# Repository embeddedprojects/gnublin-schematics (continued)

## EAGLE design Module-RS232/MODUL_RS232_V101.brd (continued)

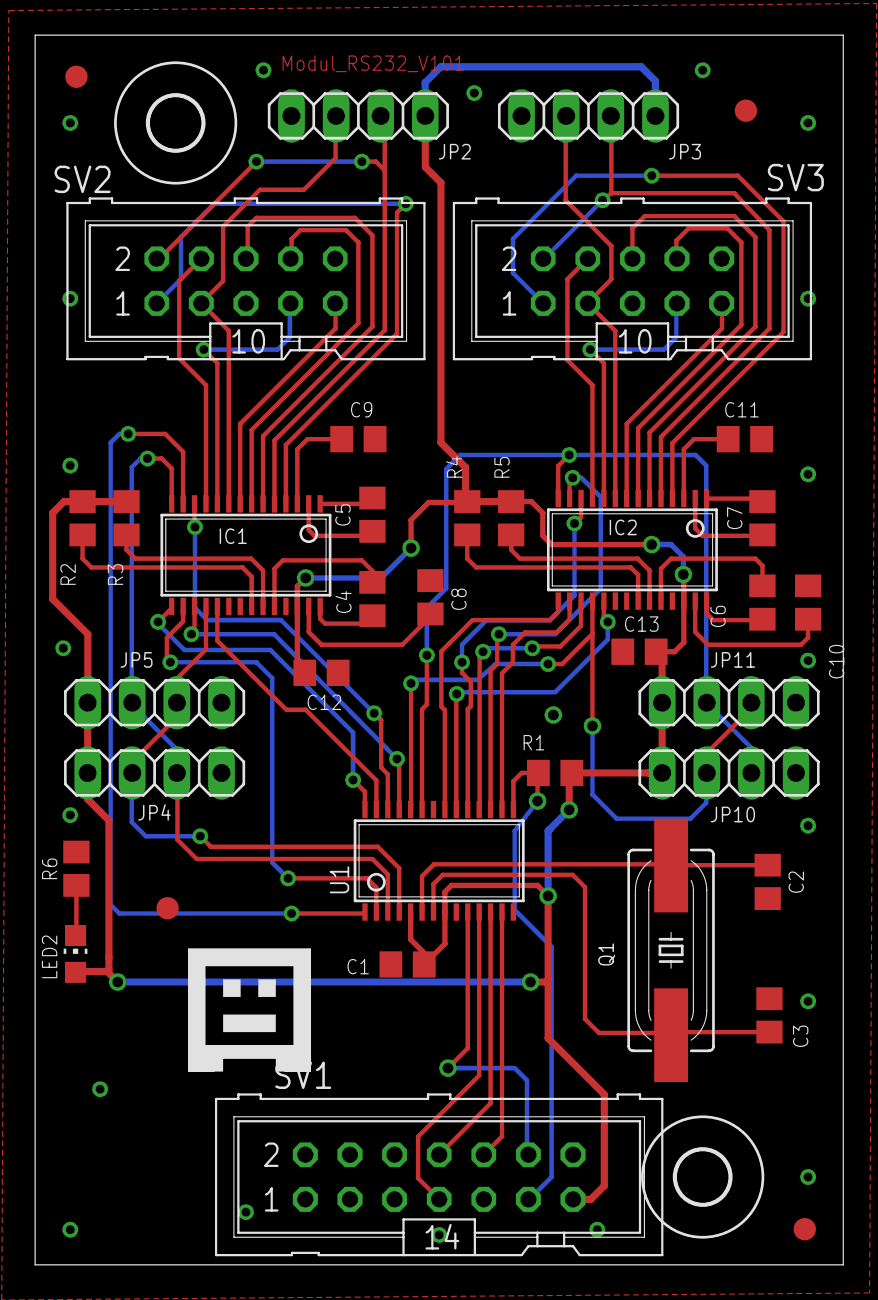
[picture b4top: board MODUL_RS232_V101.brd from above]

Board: 2 copper layers, 46.0 x 70.0 mm, 40 parts (0 on the bottom side), 58 nets.

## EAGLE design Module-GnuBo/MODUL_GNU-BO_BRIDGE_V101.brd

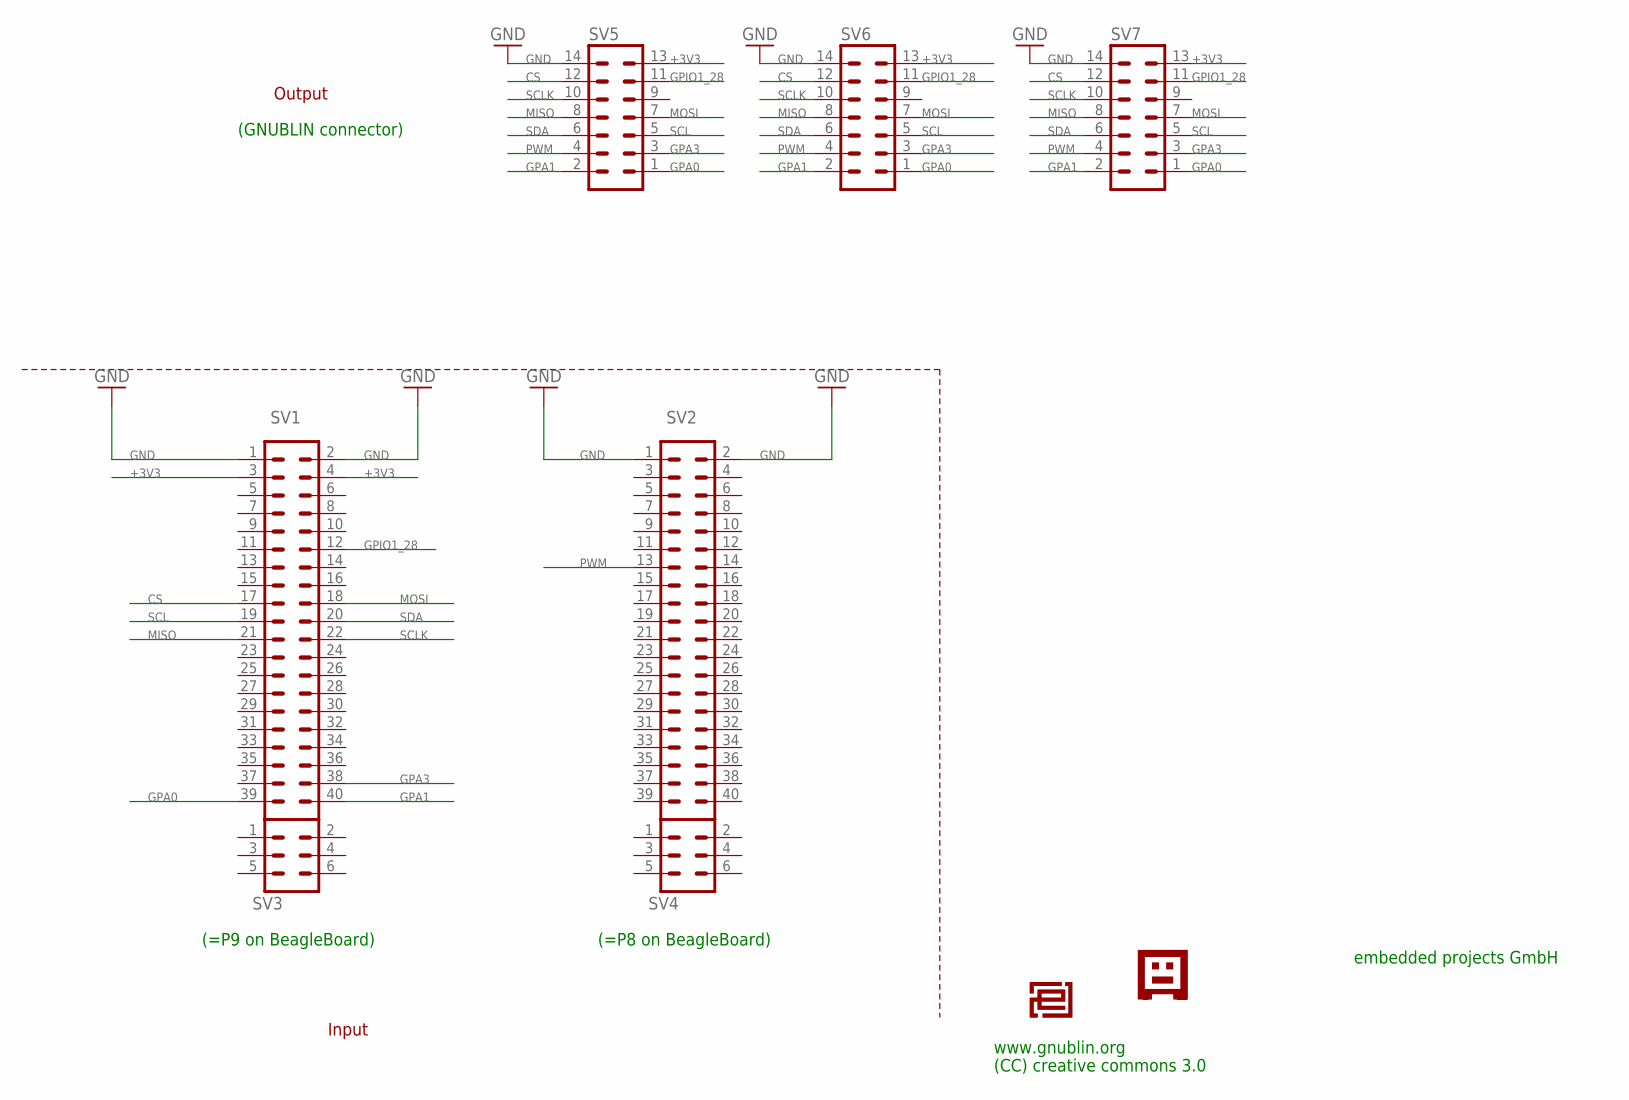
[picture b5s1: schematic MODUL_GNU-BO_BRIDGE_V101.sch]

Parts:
SV1, SV2: MA20-2
SV3, SV4: MA03-2
SV5, SV6, SV7: ML14
U$2: EPLOGOSIEB; EPLOGOSIEBDRUCK
U$3: GNUBLINLOGOSIEB; GNUSIEBDRUCK

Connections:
+3V3: SV1.3, SV1.4, SV5.13, SV6.13, SV7.13
CS: SV1.17, SV5.12, SV6.12, SV7.12
GND: SV1.1, SV1.2, SV2.1, SV2.2, SV5.14, SV6.14, SV7.14
GPA0: SV1.39, SV5.1, SV6.1, SV7.1
GPA1: SV1.40, SV5.2, SV6.2, SV7.2
GPA3: SV1.38, SV5.3, SV6.3, SV7.3
GPIO1_28: SV1.12, SV5.11, SV6.11, SV7.11
MISO: SV1.21, SV5.8, SV6.8, SV7.8
MOSI: SV1.18, SV5.7, SV6.7, SV7.7
PWM: SV2.13, SV5.4, SV6.4, SV7.4
SCL: SV1.19, SV5.5, SV6.5, SV7.5
SCLK: SV1.22, SV5.10, SV6.10, SV7.10
SDA: SV1.20, SV5.6, SV6.6, SV7.6

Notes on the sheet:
embedded projects GmbH
Input
Output
(=P9 on BeagleBoard)
(=P8 on BeagleBoard)
(GNUBLIN connector)
(CC) creative commons 3.0
www.gnublin.org

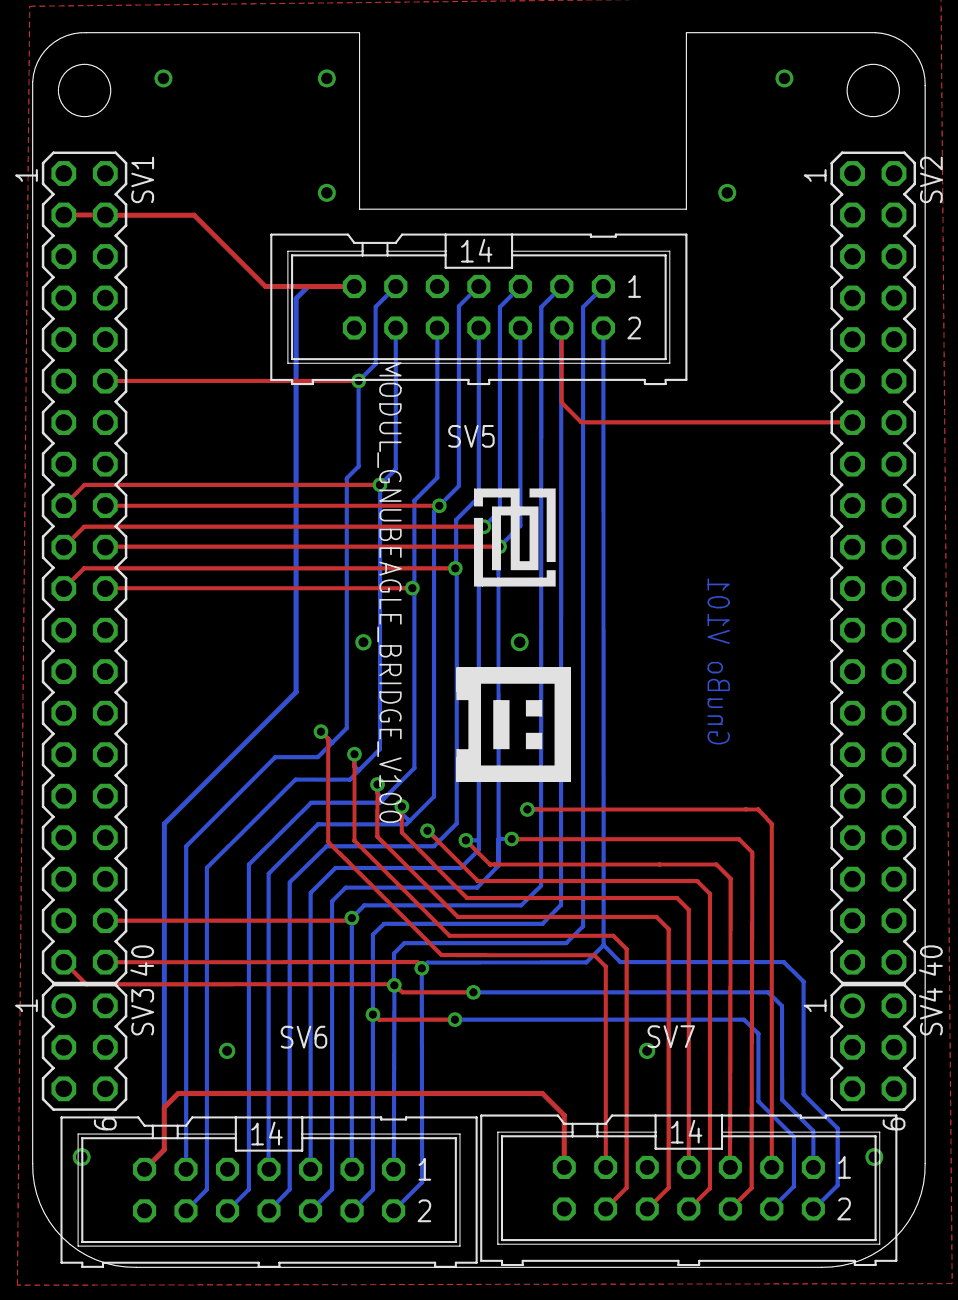
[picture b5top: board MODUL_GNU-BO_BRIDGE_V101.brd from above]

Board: 2 copper layers, 54.6 x 75.5 mm, 9 parts (0 on the bottom side), 13 nets.

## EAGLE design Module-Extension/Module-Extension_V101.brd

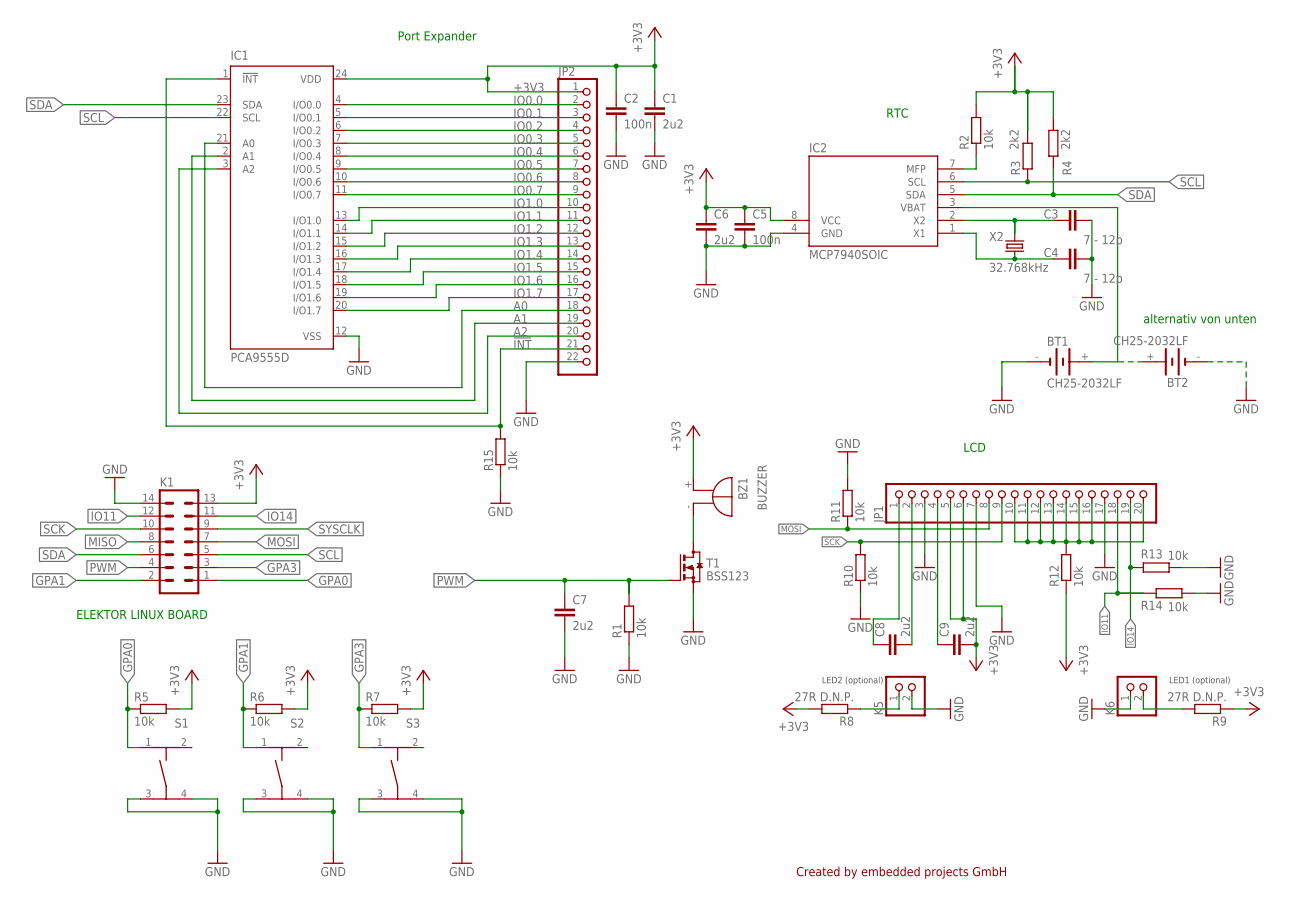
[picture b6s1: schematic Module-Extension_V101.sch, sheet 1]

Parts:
BT1, BT2: CH25-2032LF; CH25; FARNELL 2064715
BZ1: BUZZER; F/TMB
C1, C6, C7, C8, C9: 2u2; C0805
C2, C5: 100n; C0805
C3, C4: 7 - 12p; C0805
IC1: PCA9555D; SO24
IC2: MCP7940SOIC; SOIC-8
JP1: PINHD-1X20; 1X20
JP2: PINHD-1X22; 1X22
K1: ML14
K5, K6: PINHD-1X2; 1X02
R1, R2, R5, R6, R7, R10, R11, R12, R13, R14, R15: 10k; R0805
R3, R4: 2k2; R0805
R8, R9: 27R D.N.P.; R0805
S1, S2, S3: ERGAENZUNG_TASTER-9314_SMD
T1: BSS123; SOT23
X2: 32.768kHz; TC26H

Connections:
!INT: IC1.1 (!INT), JP2.21, R15.2
+3V3: BZ1.+, C1.1, C2.1, C5.1, C6.1, C9.2, IC1.24 (VDD), IC2.8 (VCC), JP1.5, JP1.6, JP2.1, K1.13, R2.2, R3.2, R4.2, R5.2, R6.2, R7.2, R8.2, R9.1, R12.1; also elsewhere on the board
A0: IC1.21 (A0), JP2.18
A1: IC1.2 (A1), JP2.19
A2: IC1.3 (A2), JP2.20
GND: BT1.-, BT2.-, C1.2, C2.2, C3.2, C4.2, C5.2, C6.2, C7.2, IC1.12 (VSS), IC2.4 (GND), JP1.3, JP1.7, JP1.17, JP2.22, K1.14, K5.2, K6.1, R1.1, R10.1, R11.2, R13.1, R14.1, R15.1, S1.3, S1.4, S2.3, S2.4, S3.3, S3.4, T1.2 (S); also elsewhere on the board
GPA0: K1.1, R5.1, S1.1
GPA1: K1.2, R6.1, S2.1
GPA3: K1.3, R7.1, S3.1
IO0.0: IC1.4 (I/O0.0), JP2.2
IO0.1: IC1.5 (I/O0.1), JP2.3
IO0.2: IC1.6 (I/O0.2), JP2.4
IO0.3: IC1.7 (I/O0.3), JP2.5
IO0.4: IC1.8 (I/O0.4), JP2.6
IO0.5: IC1.9 (I/O0.5), JP2.7
IO0.6: IC1.10 (I/O0.6), JP2.8
IO0.7: IC1.11 (I/O0.7), JP2.9
IO1.0: IC1.13 (I/O1.0), JP2.10
IO1.1: IC1.14 (I/O1.1), JP2.11
IO1.2: IC1.15 (I/O1.2), JP2.12
IO1.3: IC1.16 (I/O1.3), JP2.13
IO1.4: IC1.17 (I/O1.4), JP2.14
IO1.5: IC1.18 (I/O1.5), JP2.15
IO1.6: IC1.19 (I/O1.6), JP2.16
IO1.7: IC1.20 (I/O1.7), JP2.17
IO11: JP1.18, K1.12, R14.2
IO14: JP1.19, K1.11, R13.2
MISO: K1.8
MOSI: JP1.8, K1.7, R11.1
unnamed: C8.1, JP1.1
unnamed: BZ1.-, T1.3 (D)
unnamed: IC2.7 (MFP), R2.1
unnamed: C3.1, IC2.2 (X2), X2.1
unnamed: C8.2, JP1.2
unnamed: C9.1, JP1.4
unnamed: K5.1, R8.1
unnamed: K6.2, R9.2
unnamed: JP1.10, JP1.11, JP1.12, JP1.13, JP1.14, JP1.15, JP1.16, JP1.20, R12.2
unnamed: C4.1, IC2.1 (X1), X2.2
PWM: C7.1, K1.4, R1.2, T1.1 (G)
SCK: JP1.9, K1.10, R10.2
SCL: IC1.22 (SCL), IC2.6 (SCL), K1.5, R3.1
SDA: IC1.23 (SDA), IC2.5 (SDA), K1.6, R4.1
SYSCLK: K1.9
VBAT: BT1.+, BT2.+, IC2.3 (VBAT)

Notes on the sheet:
LCD
Port Expander
RTC
ELEKTOR LINUX BOARD
LED1 (optional)
LED2 (optional)
Created by embedded projects GmbH
alternativ von unten

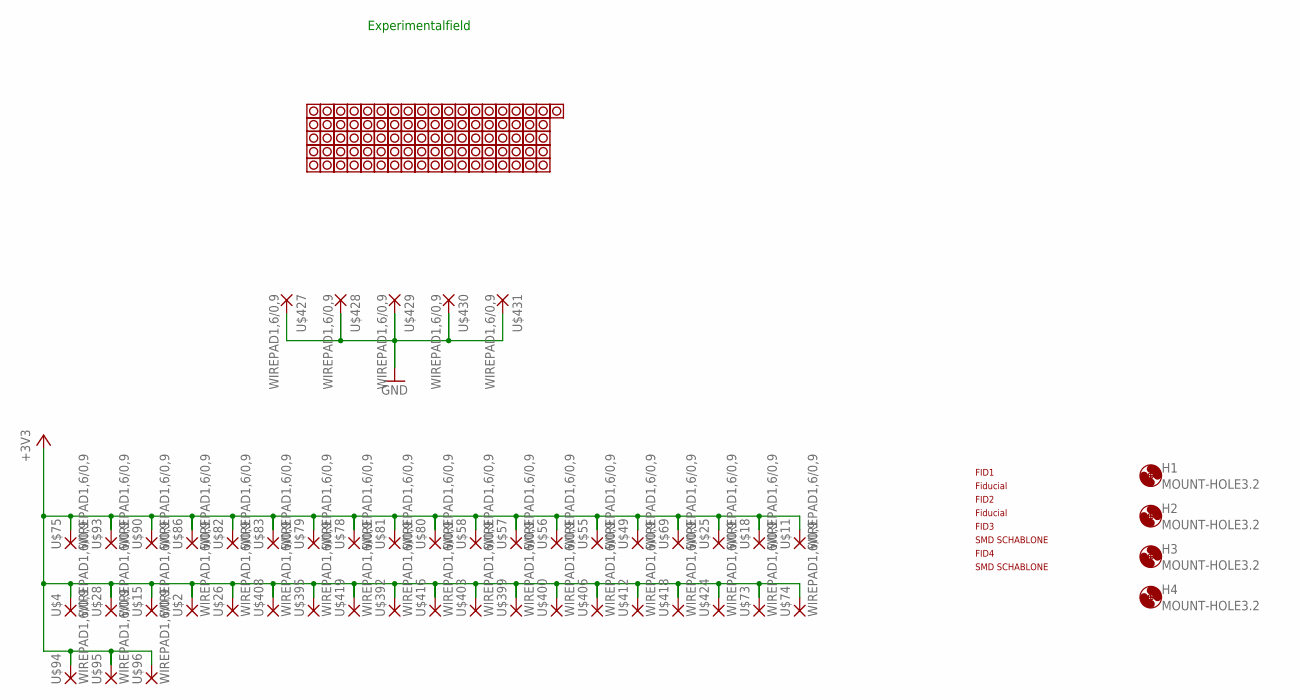
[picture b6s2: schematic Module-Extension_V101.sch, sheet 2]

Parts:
FID1, FID2, FID3, FID4: PASSERMARKEN_FIDUCIAL
H1, H2, H3, H4: MOUNT-HOLE3.2; 3,2
U$2, U$4, U$11, U$15, U$18, U$25, U$26, U$28, U$49, U$55, U$56, U$57, U$58, U$69, U$73, U$74, U$75, U$78, U$79, U$80, U$81, U$82, U$83, U$86, U$90, U$93, U$94, U$95, U$96, U$392, U$395, U$399, U$400, U$403, U$406, U$408, U$412, U$416, U$418, U$419, U$424, U$427, U$428, U$429, U$430, U$431: WIREPAD1,6/0,9; 1,6/0,9
U$3, U$5, U$6, U$7, U$8, U$9, U$10, U$12, U$13, U$14, U$16, U$17, U$19, U$20, U$21, U$22, U$23, U$24, U$27, U$29, U$30, U$31, U$32, U$33, U$34, U$35, U$36, U$37, U$38, U$39, U$40, U$41, U$42, U$43, U$44, U$45, U$46, U$47, U$48, U$50, U$51, U$52, U$53, U$54, U$59, U$60, U$61, U$62, U$63, U$64, U$65, U$66, U$67, U$68, U$70, U$71, U$72, U$76, U$77, U$84, U$85, U$87, U$88, U$89, U$91, U$92, U$391, U$393, U$394, U$396, U$397, U$398, U$401, U$402, U$404, U$405, U$407, U$409, U$410, U$411, U$413, U$414, U$415, U$417, U$420, U$421, U$422, U$423, U$425, U$426, U$432: VIAS

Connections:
+3V3: U$2.1, U$4.1, U$11.1, U$15.1, U$18.1, U$25.1, U$26.1, U$28.1, U$49.1, U$55.1, U$56.1, U$57.1, U$58.1, U$69.1, U$73.1, U$74.1, U$75.1, U$78.1, U$79.1, U$80.1, U$81.1, U$82.1, U$83.1, U$86.1, U$90.1, U$93.1, U$94.1, U$95.1, U$96.1, U$392.1, U$395.1, U$399.1, U$400.1, U$403.1, U$406.1, U$408.1, U$412.1, U$416.1, U$418.1, U$419.1, U$424.1; also elsewhere on the board
GND: U$427.1, U$428.1, U$429.1, U$430.1, U$431.1; also elsewhere on the board

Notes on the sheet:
Experimentalfield

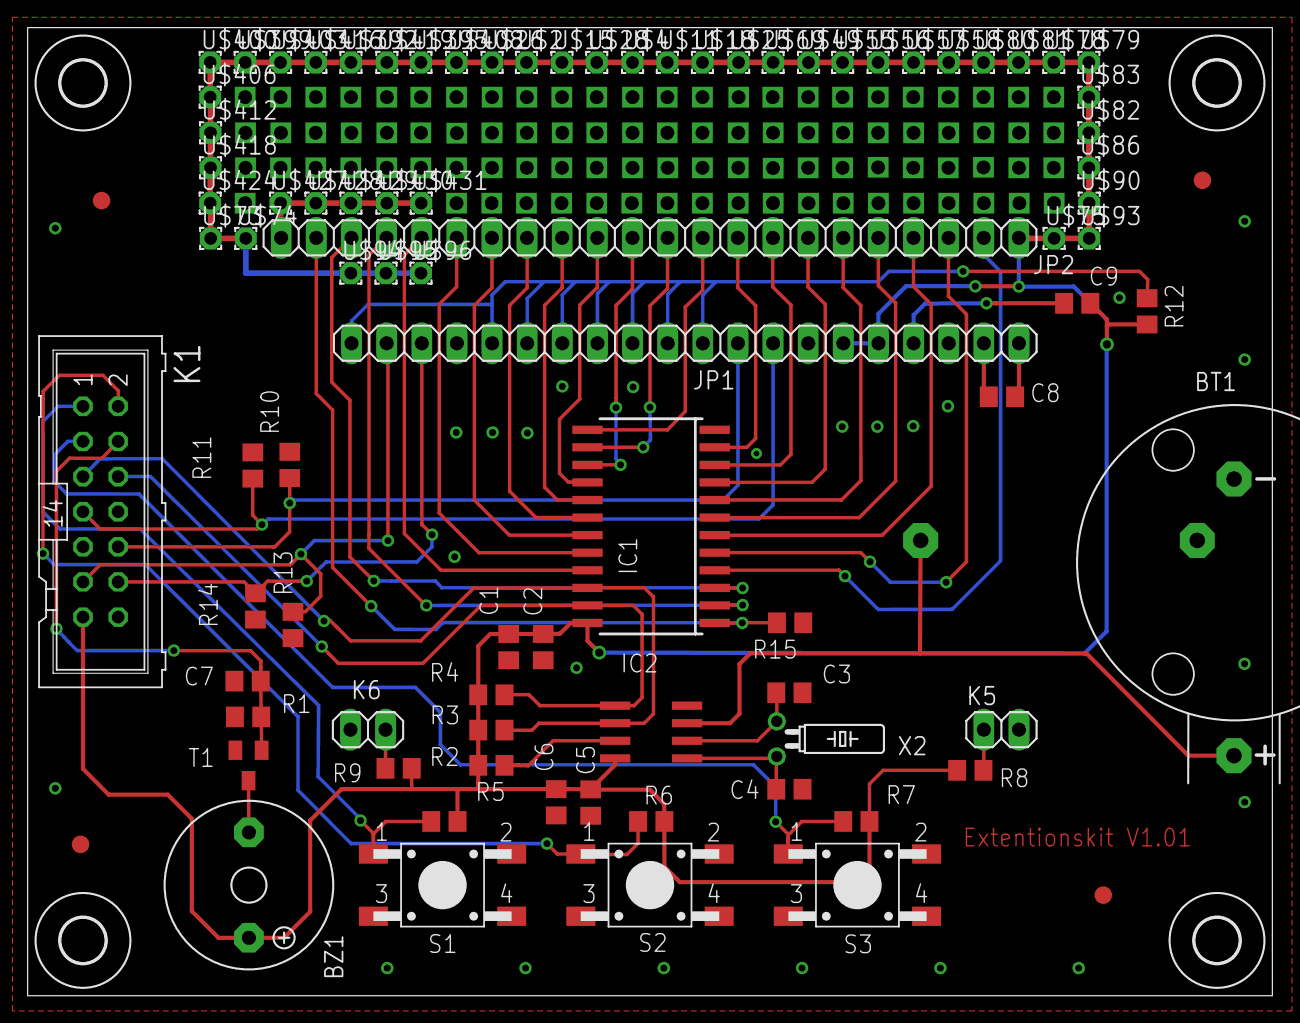
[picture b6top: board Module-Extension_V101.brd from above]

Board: 2 copper layers, 90.0 x 70.0 mm, 184 parts (1 on the bottom side), 43 nets.

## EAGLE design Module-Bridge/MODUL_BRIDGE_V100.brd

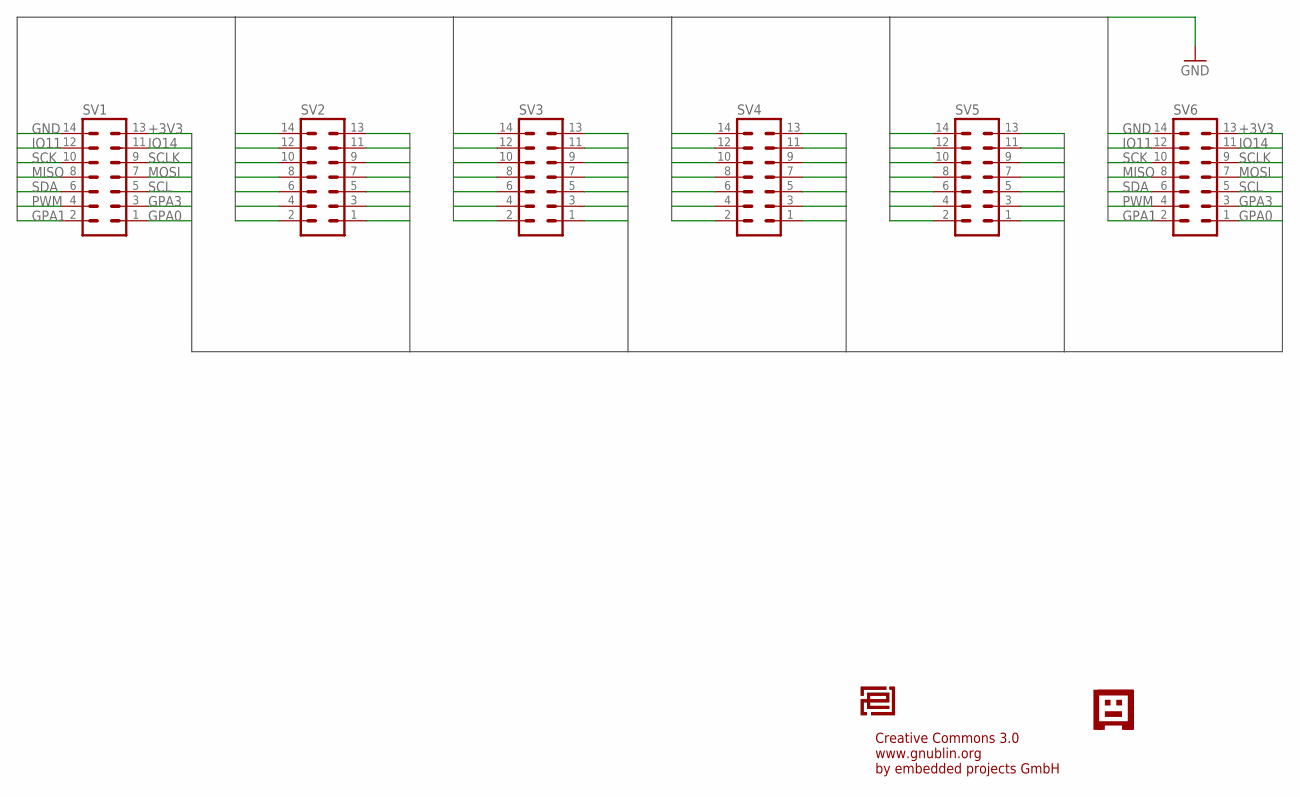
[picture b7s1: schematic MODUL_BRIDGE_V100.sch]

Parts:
SV1, SV2, SV3, SV4, SV5, SV6: ML14
U$1: EPLOGOSIEB; EPLOGOSIEBDRUCK
U$2: GNUBLINLOGOSIEB; GNUSIEBDRUCK

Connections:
+3V3: SV1.13, SV2.13, SV3.13, SV4.13, SV5.13, SV6.13
GND: SV1.14, SV2.14, SV3.14, SV4.14, SV5.14, SV6.14
GPA0: SV1.1, SV2.1, SV3.1, SV4.1, SV5.1, SV6.1
GPA1: SV1.2, SV2.2, SV3.2, SV4.2, SV5.2, SV6.2
GPA3: SV1.3, SV2.3, SV3.3, SV4.3, SV5.3, SV6.3
IO11: SV1.12, SV2.12, SV3.12, SV4.12, SV5.12, SV6.12
IO14: SV1.11, SV2.11, SV3.11, SV4.11, SV5.11, SV6.11
MISO: SV1.8, SV2.8, SV3.8, SV4.8, SV5.8, SV6.8
MOSI: SV1.7, SV2.7, SV3.7, SV4.7, SV5.7, SV6.7
PWM: SV1.4, SV2.4, SV3.4, SV4.4, SV5.4, SV6.4
SCK: SV1.10, SV2.10, SV3.10, SV4.10, SV5.10, SV6.10
SCL: SV1.5, SV2.5, SV3.5, SV4.5, SV5.5, SV6.5
SCLK: SV1.9, SV2.9, SV3.9, SV4.9, SV5.9, SV6.9
SDA: SV1.6, SV2.6, SV3.6, SV4.6, SV5.6, SV6.6

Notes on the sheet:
Creative Commons 3.0 www.gnublin.org by embedded projects GmbH

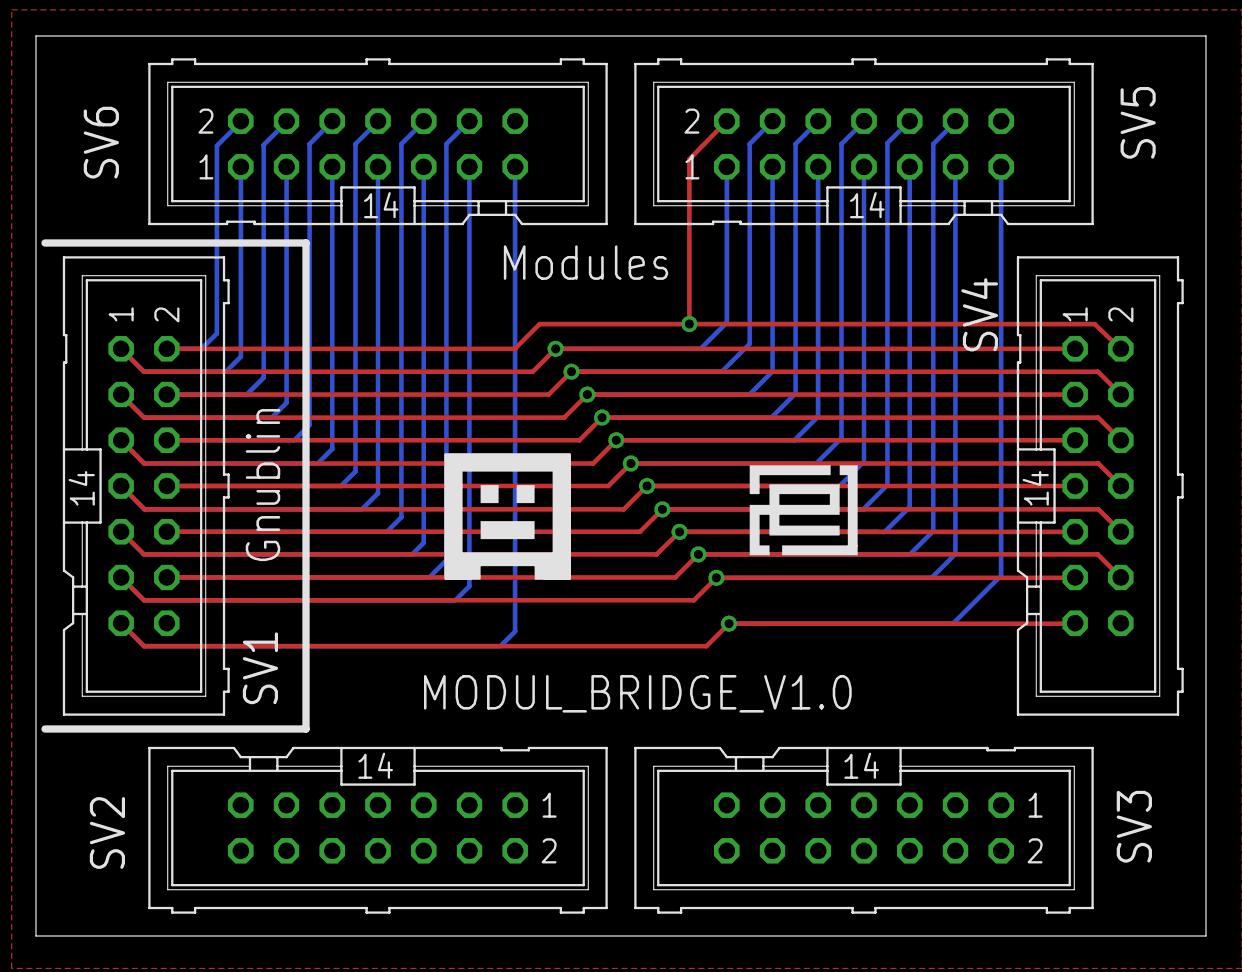
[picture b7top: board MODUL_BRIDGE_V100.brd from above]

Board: 4 copper layers, 65.0 x 50.0 mm, 8 parts (0 on the bottom side), 14 nets.

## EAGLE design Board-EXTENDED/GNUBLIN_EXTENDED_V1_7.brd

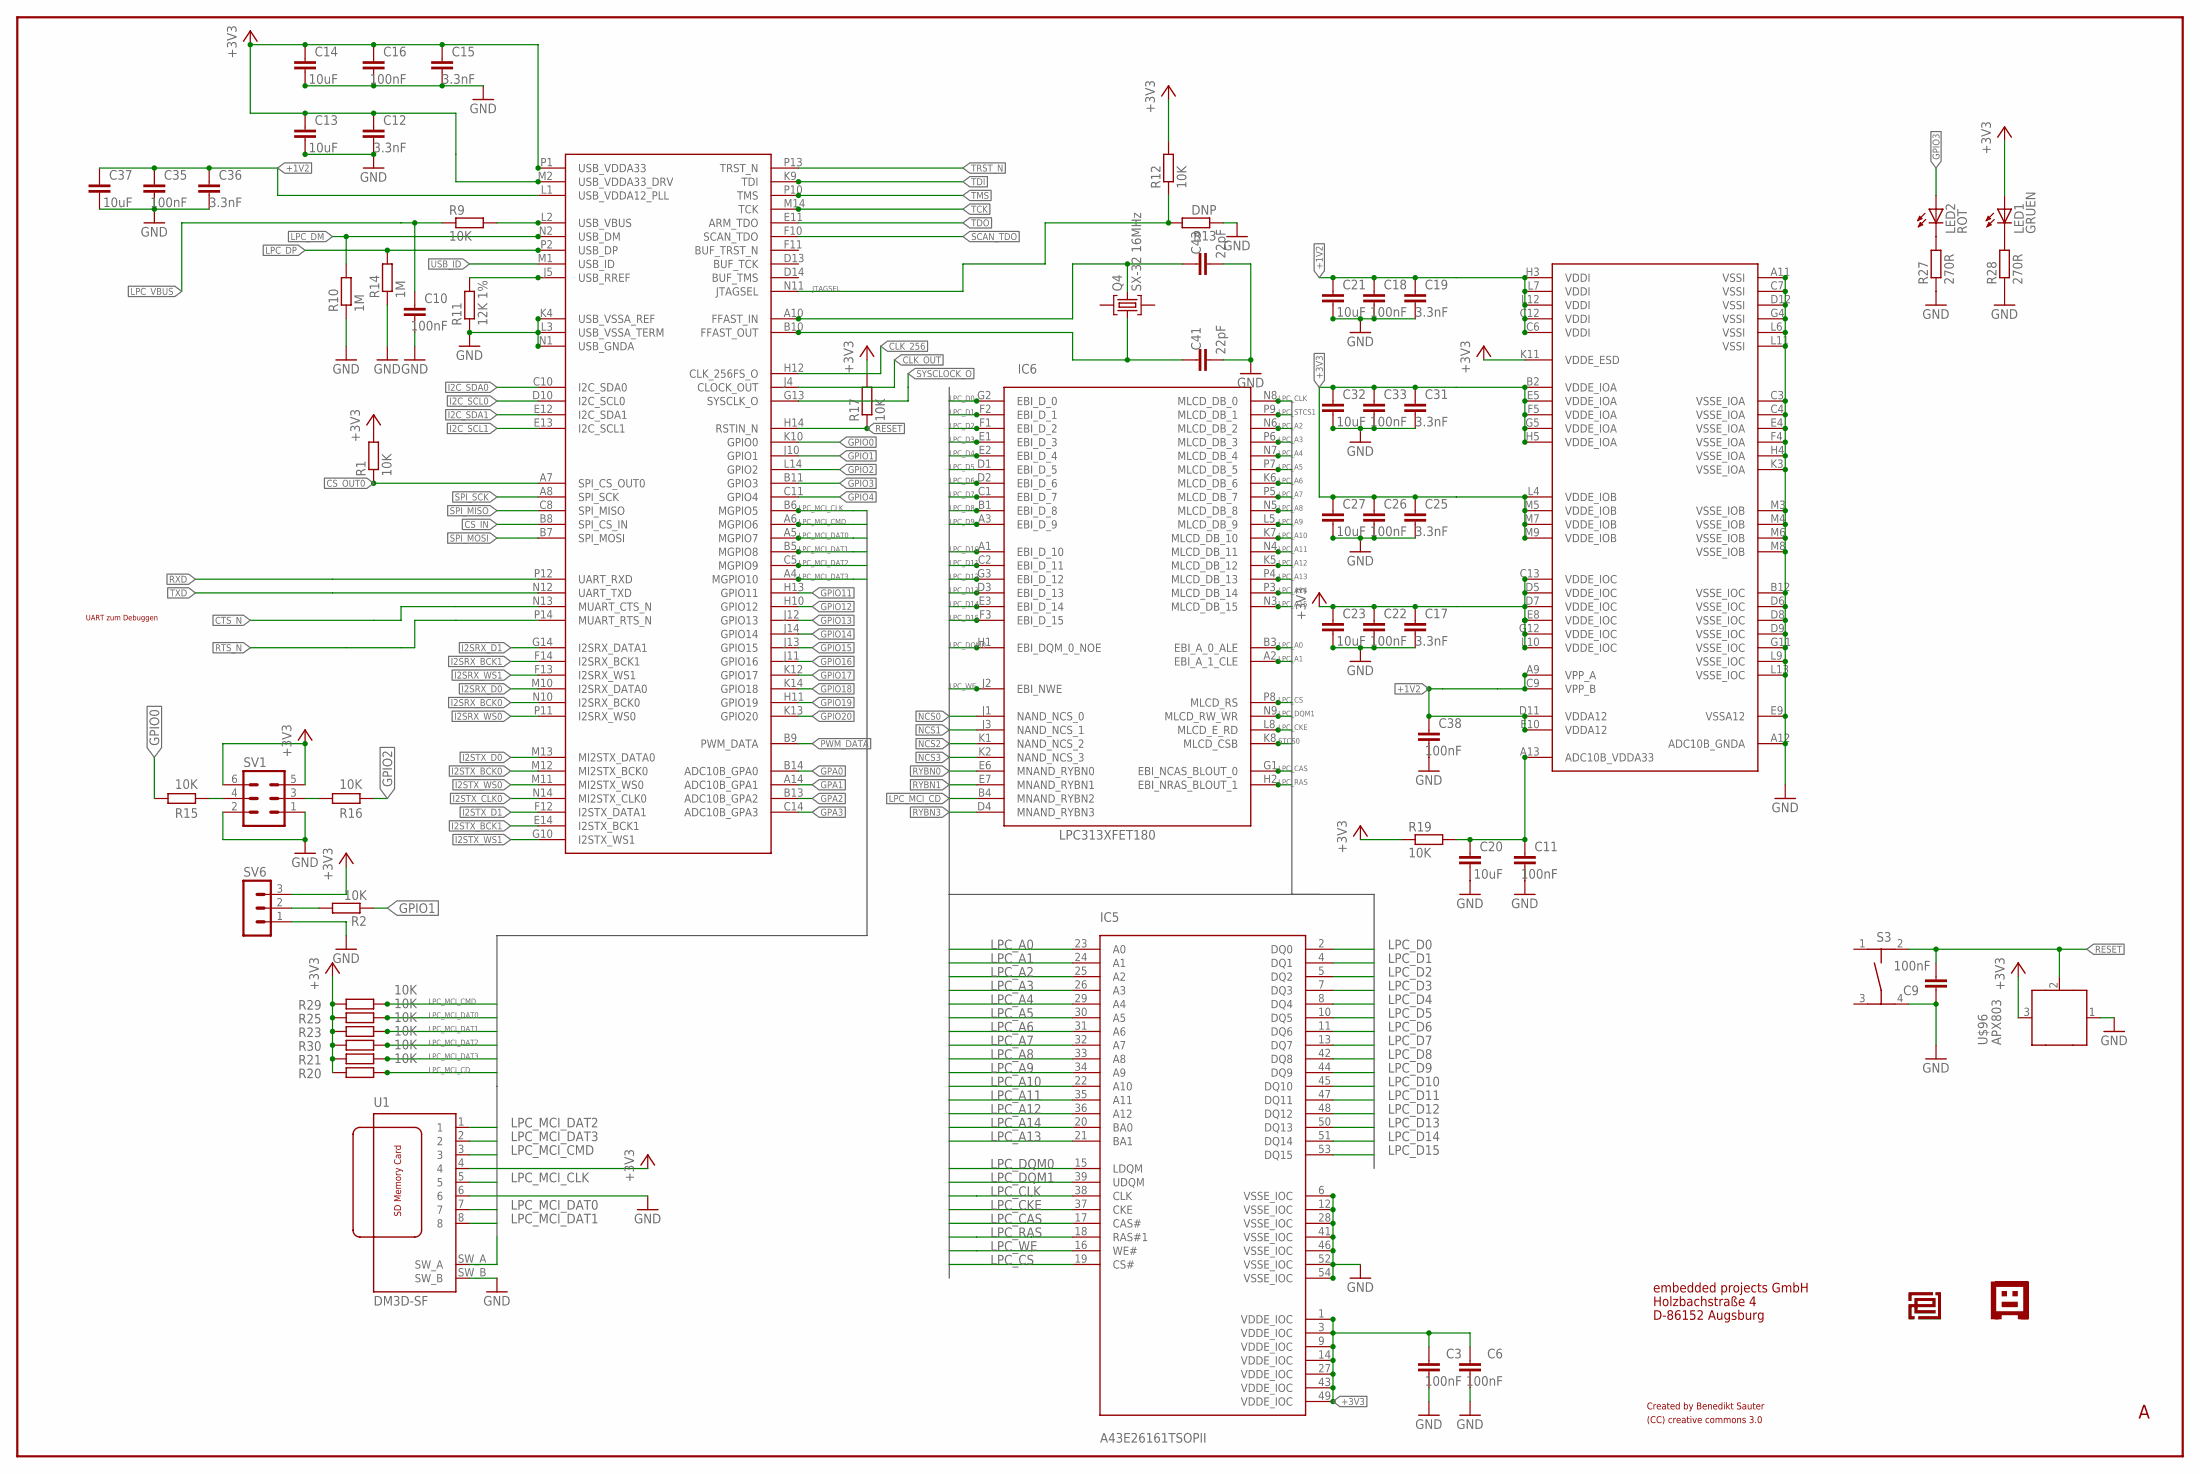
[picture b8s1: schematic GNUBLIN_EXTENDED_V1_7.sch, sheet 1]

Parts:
C3, C6, C9, C10, C11, C16, C18, C22, C26, C33, C35, C38: 100nF; C0805
C12, C15, C17, C19, C25, C31, C36: 3.3nF; C0805
C13, C14, C20, C21, C23, C27, C32, C37: 10uF; C0805
C41, C43: 22pF; C0805
IC5: A43E26161TSOPII; TSOPII
IC6: LPC313XFET180; TFBGA180
LED1: GRUEN; CHIP-LED0805
LED2: ROT; CHIP-LED0805
Q4: SX-32 16MHz; SX-32; FARNELL 1712841
R1, R2, R9, R12, R15, R16, R17, R19, R20, R21, R23, R25, R29, R30: 10K; R0805
R10, R14: 1M; R0805
R11: 12K 1%; R0805
R13: DNP; R0805
R27, R28: 270R; R0805
S3: TASTER-9314_SMD
SV1: MA03-2
SV6: MA03-1
U1: DM3D-SF
U$1: EPLOGOSIEB; EPLOGOSIEBDRUCK
U$2: GNUBLINLOGOSIEB; GNUSIEBDRUCK
U$96: APX803; SOT23

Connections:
+1V2: C18.2, C19.2, C21.2, C35.2, C36.2, C37.2, C38.2, IC6.A9 (VPP_A), IC6.C6 (VDDI), IC6.C9 (VPP_B), IC6.C12 (VDDI), IC6.D11 (VDDA12), IC6.E10 (VDDA12), IC6.H3 (VDDI), IC6.L1 (USB_VDDA12_PLL), IC6.L7 (VDDI), IC6.L12 (VDDI); also elsewhere on the board
+3V3: C3.2, C6.2, C12.2, C13.2, C14.2, C15.2, C16.2, C17.2, C22.2, C23.2, C25.2, C26.2, C27.2, C31.2, C32.2, C33.2, IC5.1 (VDDE_IOC), IC5.3 (VDDE_IOC), IC5.9 (VDDE_IOC), IC5.14 (VDDE_IOC), IC5.27 (VDDE_IOC), IC5.43 (VDDE_IOC), IC5.49 (VDDE_IOC), IC6.B2 (VDDE_IOA), IC6.C13 (VDDE_IOC), IC6.D5 (VDDE_IOC), IC6.D7 (VDDE_IOC), IC6.E5 (VDDE_IOA), IC6.E8 (VDDE_IOC), IC6.F5 (VDDE_IOA), IC6.G5 (VDDE_IOA), IC6.G12 (VDDE_IOC), IC6.H5 (VDDE_IOA), IC6.K11 (VDDE_ESD), IC6.L4 (VDDE_IOB), IC6.L10 (VDDE_IOC), IC6.M2 (USB_VDDA33_DRV), IC6.M5 (VDDE_IOB), IC6.M7 (VDDE_IOB), IC6.M9 (VDDE_IOB), IC6.P1 (USB_VDDA33), LED1.A, R1.2, R12.2, R17.2, R19.1, R20.1, R21.1, R23.1, R25.1, R29.1, R30.1, SV1.5, SV1.6, SV6.3, U1.4, U$96.3 (VCC); also elsewhere on the board
CLK_256: IC6.H12 (CLK_256FS_O); also elsewhere on the board
CLK_OUT: IC6.J4 (CLOCK_OUT); also elsewhere on the board
CS_IN: IC6.B8 (SPI_CS_IN); also elsewhere on the board
CS_OUT0: IC6.A7 (SPI_CS_OUT0), R1.1; also elsewhere on the board
CTS_N: IC6.N13 (MUART_CTS_N); also elsewhere on the board
GND: C3.1, C6.1, C9.2, C10.1, C11.1, C12.1, C13.1, C14.1, C15.1, C16.1, C17.1, C18.1, C19.1, C20.1, C21.1, C22.1, C23.1, C25.1, C26.1, C27.1, C31.1, C32.1, C33.1, C35.1, C36.1, C37.1, C38.1, C41.1, C43.1, IC5.6 (VSSE_IOC), IC5.12 (VSSE_IOC), IC5.28 (VSSE_IOC), IC5.41 (VSSE_IOC), IC5.46 (VSSE_IOC), IC5.52 (VSSE_IOC), IC5.54 (VSSE_IOC), IC6.A11 (VSSI), IC6.A12 (ADC10B_GNDA), IC6.B12 (VSSE_IOC), IC6.C3 (VSSE_IOA), IC6.C4 (VSSE_IOA), IC6.C7 (VSSI), IC6.D6 (VSSE_IOC), IC6.D8 (VSSE_IOC), IC6.D9 (VSSE_IOC), IC6.D12 (VSSI), IC6.E4 (VSSE_IOA), IC6.E9 (VSSA12), IC6.F4 (VSSE_IOA), IC6.G4 (VSSI), IC6.G11 (VSSE_IOC), IC6.H4 (VSSE_IOA), IC6.K3 (VSSE_IOA), IC6.K4 (USB_VSSA_REF), IC6.L3 (USB_VSSA_TERM), IC6.L6 (VSSI), IC6.L9 (VSSE_IOC), IC6.L11 (VSSI), IC6.L13 (VSSE_IOC), IC6.M3 (VSSE_IOB), IC6.M4 (VSSE_IOB), IC6.M6 (VSSE_IOB), IC6.M8 (VSSE_IOB), IC6.N1 (USB_GNDA), R10.1, R11.1, R13.1, R14.1, R27.1, R28.1, S3.4, SV1.1, SV1.2, SV6.1, U1.6, U1.SW_B, U$96.1 (GND); also elsewhere on the board
GPA0: IC6.B14 (ADC10B_GPA0); also elsewhere on the board
GPA1: IC6.A14 (ADC10B_GPA1); also elsewhere on the board
GPA2: IC6.B13 (ADC10B_GPA2); also elsewhere on the board
GPA3: IC6.C14 (ADC10B_GPA3); also elsewhere on the board
GPIO0: IC6.K10 (GPIO0), R15.1; also elsewhere on the board
GPIO1: IC6.J10 (GPIO1), R2.1; also elsewhere on the board
GPIO2: IC6.L14 (GPIO2), R16.2; also elsewhere on the board
GPIO3: IC6.B11 (GPIO3), LED2.A; also elsewhere on the board
GPIO4: IC6.C11 (GPIO4); also elsewhere on the board
GPIO11: IC6.H13 (GPIO11); also elsewhere on the board
GPIO12: IC6.H10 (GPIO12); also elsewhere on the board
GPIO13: IC6.J12 (GPIO13); also elsewhere on the board
GPIO14: IC6.J14 (GPIO14); also elsewhere on the board
GPIO15: IC6.J13 (GPIO15); also elsewhere on the board
GPIO16: IC6.J11 (GPIO16); also elsewhere on the board
GPIO17: IC6.K12 (GPIO17); also elsewhere on the board
GPIO18: IC6.K14 (GPIO18); also elsewhere on the board
GPIO19: IC6.H11 (GPIO19); also elsewhere on the board
GPIO20: IC6.K13 (GPIO20); also elsewhere on the board
I2C_SCL0: IC6.D10 (I2C_SCL0); also elsewhere on the board
I2C_SCL1: IC6.E13 (I2C_SCL1); also elsewhere on the board
I2C_SDA0: IC6.C10 (I2C_SDA0); also elsewhere on the board
I2C_SDA1: IC6.E12 (I2C_SDA1); also elsewhere on the board
I2SRX_BCK0: IC6.N10 (I2SRX_BCK0); also elsewhere on the board
I2SRX_BCK1: IC6.F14 (I2SRX_BCK1); also elsewhere on the board
I2SRX_D0: IC6.M10 (I2SRX_DATA0); also elsewhere on the board
I2SRX_D1: IC6.G14 (I2SRX_DATA1); also elsewhere on the board
I2SRX_WS0: IC6.P11 (I2SRX_WS0); also elsewhere on the board
I2SRX_WS1: IC6.F13 (I2SRX_WS1); also elsewhere on the board
I2STX_BCK0: IC6.M12 (MI2STX_BCK0); also elsewhere on the board
I2STX_BCK1: IC6.E14 (I2STX_BCK1); also elsewhere on the board
I2STX_CLK0: IC6.N14 (MI2STX_CLK0); also elsewhere on the board
I2STX_D0: IC6.M13 (MI2STX_DATA0); also elsewhere on the board
I2STX_D1: IC6.F12 (I2STX_DATA1); also elsewhere on the board
I2STX_WS0: IC6.M11 (MI2STX_WS0); also elsewhere on the board
I2STX_WS1: IC6.G10 (I2STX_WS1); also elsewhere on the board
IO0: R15.2, SV1.4
IO2: R16.1, SV1.3
JTAGSEL: IC6.N11 (JTAGSEL), R12.1, R13.2
LPC_A0: IC5.23 (A0), IC6.B3 (EBI_A_0_ALE); also elsewhere on the board
LPC_A1: IC5.24 (A1), IC6.A2 (EBI_A_1_CLE); also elsewhere on the board
LPC_A2: IC5.25 (A2), IC6.N6 (MLCD_DB_2); also elsewhere on the board
LPC_A3: IC5.26 (A3), IC6.P6 (MLCD_DB_3); also elsewhere on the board
LPC_A4: IC5.29 (A4), IC6.N7 (MLCD_DB_4); also elsewhere on the board
LPC_A5: IC5.30 (A5), IC6.P7 (MLCD_DB_5); also elsewhere on the board
LPC_A6: IC5.31 (A6), IC6.K6 (MLCD_DB_6); also elsewhere on the board
LPC_A7: IC5.32 (A7), IC6.P5 (MLCD_DB_7); also elsewhere on the board
LPC_A8: IC5.33 (A8), IC6.N5 (MLCD_DB_8); also elsewhere on the board
LPC_A9: IC5.34 (A9), IC6.L5 (MLCD_DB_9); also elsewhere on the board
LPC_A10: IC5.22 (A10), IC6.K7 (MLCD_DB_10); also elsewhere on the board
LPC_A11: IC5.35 (A11), IC6.N4 (MLCD_DB_11); also elsewhere on the board
LPC_A12: IC5.36 (A12), IC6.K5 (MLCD_DB_12); also elsewhere on the board
LPC_A13: IC5.21 (BA1), IC6.P4 (MLCD_DB_13); also elsewhere on the board
LPC_A14: IC5.20 (BA0), IC6.P3 (MLCD_DB_14); also elsewhere on the board
LPC_A15: IC6.N3 (MLCD_DB_15); also elsewhere on the board
LPC_CAS: IC5.17 (CAS#), IC6.G1 (EBI_NCAS_BLOUT_0)
LPC_CKE: IC5.37 (CKE), IC6.L8 (MLCD_E_RD); also elsewhere on the board
LPC_CLK: IC5.38 (CLK), IC6.N8 (MLCD_DB_0)
LPC_CS: IC5.19 (CS#), IC6.P8 (MLCD_RS); also elsewhere on the board
LPC_D0: IC5.2 (DQ0), IC6.G2 (EBI_D_0); also elsewhere on the board
LPC_D1: IC5.4 (DQ1), IC6.F2 (EBI_D_1); also elsewhere on the board
LPC_D2: IC5.5 (DQ2), IC6.F1 (EBI_D_2); also elsewhere on the board
LPC_D3: IC5.7 (DQ3), IC6.E1 (EBI_D_3); also elsewhere on the board
LPC_D4: IC5.8 (DQ4), IC6.E2 (EBI_D_4); also elsewhere on the board
LPC_D5: IC5.10 (DQ5), IC6.D1 (EBI_D_5); also elsewhere on the board
LPC_D6: IC5.11 (DQ6), IC6.D2 (EBI_D_6); also elsewhere on the board
LPC_D7: IC5.13 (DQ7), IC6.C1 (EBI_D_7); also elsewhere on the board
LPC_D8: IC5.42 (DQ8), IC6.B1 (EBI_D_8); also elsewhere on the board
LPC_D9: IC5.44 (DQ9), IC6.A3 (EBI_D_9); also elsewhere on the board
LPC_D10: IC5.45 (DQ10), IC6.A1 (EBI_D_10); also elsewhere on the board
LPC_D11: IC5.47 (DQ11), IC6.C2 (EBI_D_11); also elsewhere on the board
LPC_D12: IC5.48 (DQ12), IC6.G3 (EBI_D_12); also elsewhere on the board
LPC_D13: IC5.50 (DQ13), IC6.D3 (EBI_D_13); also elsewhere on the board
LPC_D14: IC5.51 (DQ14), IC6.E3 (EBI_D_14); also elsewhere on the board
LPC_D15: IC5.53 (DQ15), IC6.F3 (EBI_D_15); also elsewhere on the board
LPC_DM: IC6.N2 (USB_DM), R10.2; also elsewhere on the board
LPC_DP: IC6.P2 (USB_DP), R14.2; also elsewhere on the board
LPC_DQM0: IC5.15 (LDQM), IC6.H1 (EBI_DQM_0_NOE); also elsewhere on the board
LPC_DQM1: IC5.39 (UDQM), IC6.N9 (MLCD_RW_WR); also elsewhere on the board
LPC_MCI_CD: IC6.B4 (MNAND_RYBN2), R20.2, U1.SW_A; also elsewhere on the board
LPC_MCI_CLK: IC6.B6 (MGPIO5), U1.5; also elsewhere on the board
LPC_MCI_CMD: IC6.A6 (MGPIO6), R29.2, U1.3; also elsewhere on the board
LPC_MCI_DAT0: IC6.A5 (MGPIO7), R25.2, U1.7; also elsewhere on the board
LPC_MCI_DAT1: IC6.B5 (MGPIO8), R23.2, U1.8; also elsewhere on the board
LPC_MCI_DAT2: IC6.C5 (MGPIO9), R30.2, U1.1; also elsewhere on the board
LPC_MCI_DAT3: IC6.A4 (MGPIO10), R21.2, U1.2; also elsewhere on the board
LPC_RAS: IC5.18 (RAS#1), IC6.H2 (EBI_NRAS_BLOUT_1)
LPC_STCS1: IC6.P9 (MLCD_DB_1)
LPC_VBUS: C10.2, R9.1; also elsewhere on the board
LPC_WE: IC5.16 (WE#), IC6.J2 (EBI_NWE); also elsewhere on the board
unnamed: LED2.C, R27.2
unnamed: R2.2, SV6.2
unnamed: LED1.C, R28.2
unnamed: C11.2, C20.2, IC6.A13 (ADC10B_VDDA33), R19.2
unnamed: IC6.J5 (USB_RREF), R11.2
unnamed: IC6.L2 (USB_VBUS), R9.2
NCS0: IC6.J1 (NAND_NCS_0); also elsewhere on the board
NCS1: IC6.J3 (NAND_NCS_1); also elsewhere on the board
NCS2: IC6.K1 (NAND_NCS_2); also elsewhere on the board
NCS3: IC6.K2 (NAND_NCS_3); also elsewhere on the board
PWM_DATA: IC6.B9 (PWM_DATA); also elsewhere on the board
RESET: C9.1, IC6.H14 (RSTIN_N), R17.1, S3.2, U$96.2 (!RESET)
RTS_N: IC6.P14 (MUART_RTS_N); also elsewhere on the board
RXD: IC6.P12 (UART_RXD); also elsewhere on the board
RYBN0: IC6.E6 (MNAND_RYBN0); also elsewhere on the board
RYBN1: IC6.E7 (MNAND_RYBN1); also elsewhere on the board
RYBN3: IC6.D4 (MNAND_RYBN3); also elsewhere on the board
SCAN_TDO: IC6.F10 (SCAN_TDO); also elsewhere on the board
SPI_MISO: IC6.C8 (SPI_MISO); also elsewhere on the board
SPI_MOSI: IC6.B7 (SPI_MOSI); also elsewhere on the board
SPI_SCK: IC6.A8 (SPI_SCK); also elsewhere on the board
STCS0: IC6.K8 (MLCD_CSB); also elsewhere on the board
SYSCLOCK_O: IC6.G13 (SYSCLK_O); also elsewhere on the board
TCK: IC6.M14 (TCK); also elsewhere on the board
TDI: IC6.K9 (TDI); also elsewhere on the board
TDO: IC6.E11 (ARM_TDO); also elsewhere on the board
TMS: IC6.P10 (TMS); also elsewhere on the board
TRST_N: IC6.P13 (TRST_N); also elsewhere on the board
TXD: IC6.N12 (UART_TXD); also elsewhere on the board
USB_ID: IC6.M1 (USB_ID); also elsewhere on the board
XTAL1: C43.2, IC6.A10 (FFAST_IN), Q4.3 (2)
XTAL2: C41.2, IC6.B10 (FFAST_OUT), Q4.1

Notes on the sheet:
embedded projects GmbH
Holzbachstraße 4
D-86152 Augsburg
Created by Benedikt Sauter
UART zum Debuggen
(CC) creative commons 3.0
